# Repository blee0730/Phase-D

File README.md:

# Phase-D

## Block Diagram

Version 1.0

Version 2.0

Version 3.0

Version 4.0

### Voltage Divider for the Thermistor

### Wheatstone Bridge for Pressure Sensor

## PCB Board

### Schematic

### PCB Layout

### Front of the PCB

### Back of the PCB

## Code

### IR Sensor Code
https://github.com/blee0730/Phase-D/assets/130094173/19ad71db-dc64-448e-8798-807aa19b2949

### PWM LED Code
https://github.com/blee0730/Phase-D/assets/130094173/cb23821e-6d77-4987-bccd-ea015186dc90

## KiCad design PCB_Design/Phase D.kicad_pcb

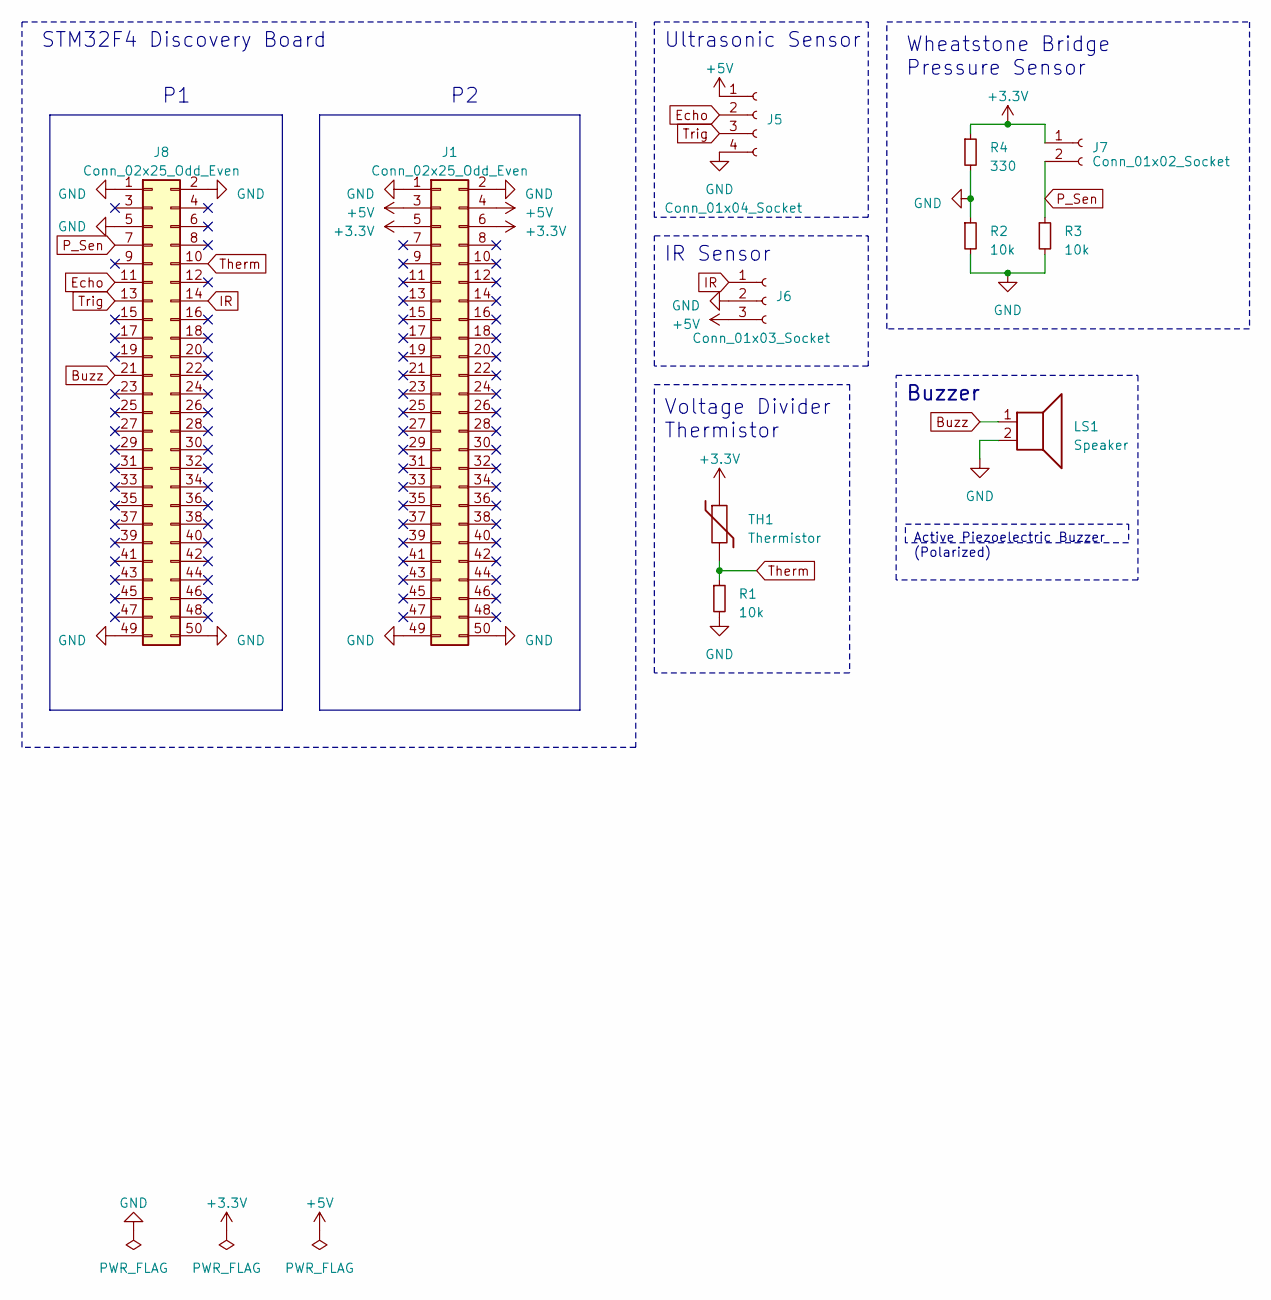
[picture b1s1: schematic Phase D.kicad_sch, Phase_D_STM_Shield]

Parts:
J1, J8: Conn_02x25_Odd_Even; PinSocket_2x25_P2.54mm_Vertical
J5: Conn_01x04_Socket; PinSocket_1x04_P2.54mm_Vertical
J6: Conn_01x03_Socket; PinSocket_1x03_P2.54mm_Vertical
J7: Conn_01x02_Socket; PinSocket_1x02_P2.54mm_Vertical
LS1: Speaker; Buzzer_12x9.5RM7.6
R1, R2, R3: 10k; R_Axial_DIN0207_L6.3mm_D2.5mm_P7.62mm_Horizontal
R4: 330; R_Axial_DIN0207_L6.3mm_D2.5mm_P7.62mm_Horizontal
TH1: Thermistor; R_Axial_DIN0207_L6.3mm_D2.5mm_P7.62mm_Horizontal

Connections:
+3.3V: J1.5, J1.6, J7.1, R4.1, TH1.1
+5V: J1.3, J1.4, J5.1, J6.3
Buzz: J8.21, LS1.1
Echo: J5.2, J8.11
GND: J1.1, J1.2, J1.49, J1.50, J5.4, J6.2, J8.1, J8.2, J8.5, J8.49, J8.50, LS1.2, R1.2, R2.1, R2.2, R3.2, R4.2
IR: J6.1, J8.14
P_Sen: J7.2, J8.7, R3.1
Therm: J8.10, R1.1, TH1.2
Trig: J5.3, J8.13

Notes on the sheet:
Active Piezoelectric Buzzer (Polarized)
Wheatstone Bridge Pressure Sensor
STM32F4 Discovery Board
Buzzer
Ultrasonic Sensor
Voltage Divider Thermistor
IR Sensor

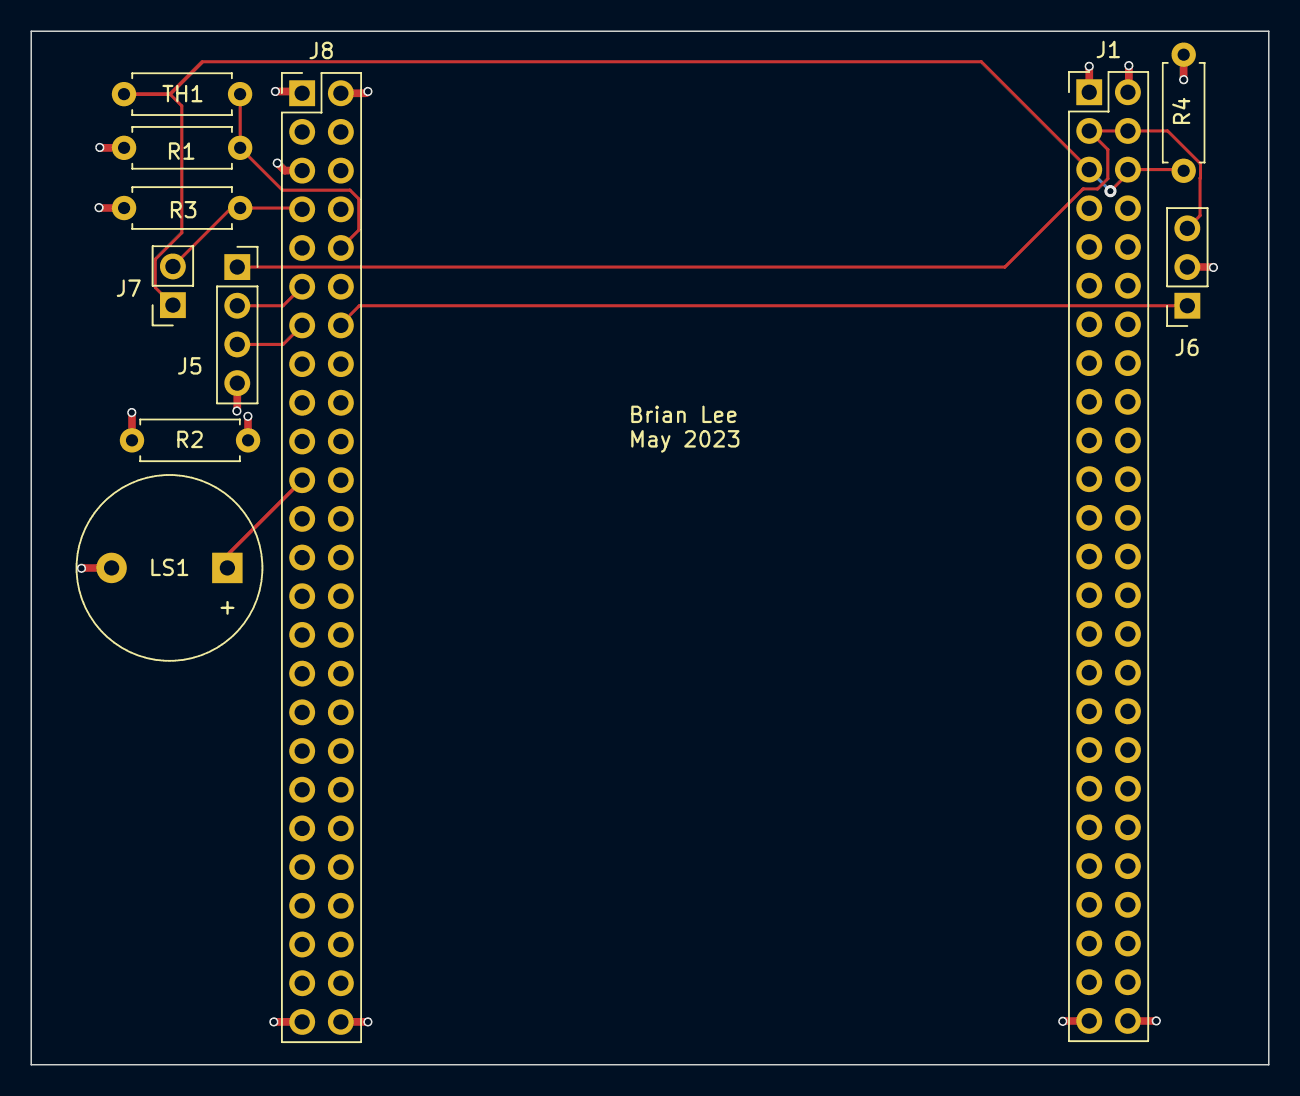
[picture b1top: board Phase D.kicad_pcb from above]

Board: 2 copper layers, 81.2 x 67.8 mm, 11 parts (0 on the bottom side), 9 nets.
